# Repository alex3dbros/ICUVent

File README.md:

# ICUVent

Video Overview: https://youtu.be/w7vbeYg_BhQ

This project is opensource and there are no guarantees given that this device 
will perform the actions that it's needed to be. Please use it with care and 
under the surveilance of professionals.

Project Structure:

Inside 3DModels folder you have the solidworks 2019 and STL files 
Inside programming you will have the programming code used to control the device.
We started with Arduino Nano, stepper Driver and nema 23 motor.

You have the schematics of the circuit attached as well.

Parts used that must be purchased: 

Mechanics:
4 x 8mm round bearings from 3d printer
2 x 8mm rods
1 x Nema 34 Motor // Updated from nema 23, will update the design soon.
1 x 16 mm T5 belt
2 x 18 teeth T5 gear
1 x Ambubag, preferable with PEEP valve and safety valve

Electronics: 
1 x Teensy 3.2
1 x Driver PSD8079-2P
1 x Encoder like this : https://www.amazon.com/Cylewet-Encoder-Digital-Potentiometer-Arduino/dp/B07DM2YMT4/ref=sr_1_6?keywords=encoder&qid=1585150874&sr=8-6
1 x DC to DC 24V to 5V like this : https://www.amazon.com/6-5-28V-MP1584-DC-DC-Step-Down-Module/dp/B082957QHR/ref=sr_1_3?keywords=MP1584+5V&qid=1585150582&sr=8-3
1 x 24 V Power supply
1 x EndStop switch
1 x raspberry pi with 7 inch display
1 x MPXV5004DP
1 x MPXV5010DP

Connection pins - https://www.amazon.com/Hotop-Pack-Single-Header-Connector/dp/B06XR8CV8P/ref=sr_1_1?keywords=2.54+pins&qid=1585151123&sr=8-1&swrs=BA6CC27AC84D7760BA1186A07738C3A9

https://www.amazon.com/DEYUE-Jumper-Wires-Set-breadboard/dp/B07LFCLMGW/ref=sr_1_10?keywords=jumper+wires&qid=1585151157&sr=8-10

Connection wires

Some info about how I built it:

I 3D printed parts and cut at the CNC the larger ones.
Here's a video with the machine functional

All the best!

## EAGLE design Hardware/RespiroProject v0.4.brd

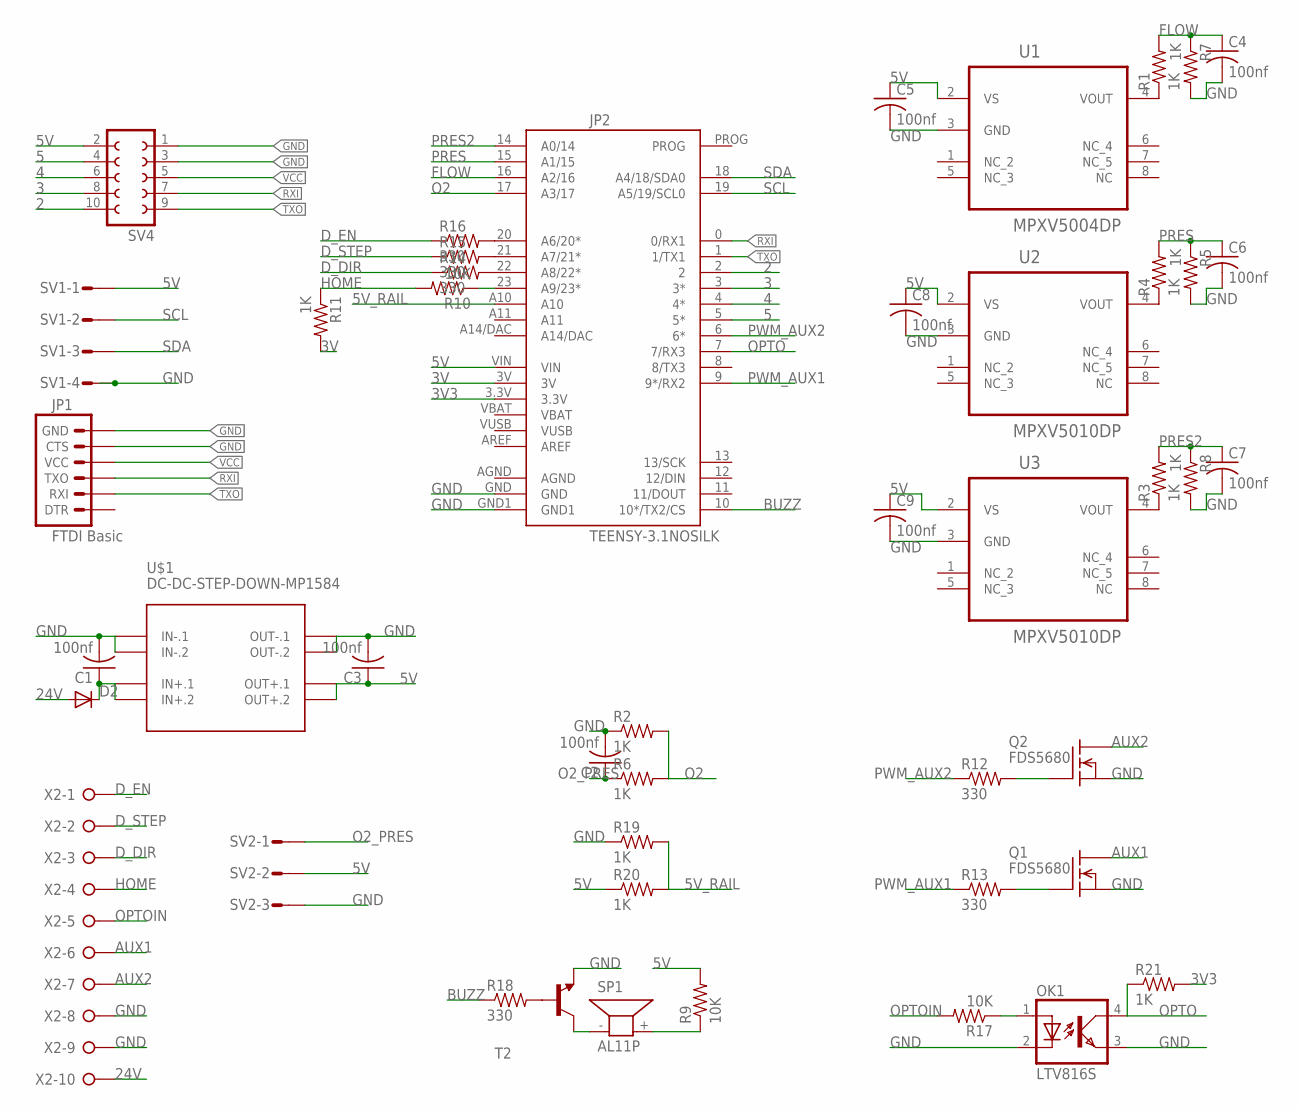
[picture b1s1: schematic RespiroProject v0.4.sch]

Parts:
C1, C2, C3, C4, C5, C6, C7, C8, C9: 100nf; C0805
D2: DIODE-MINIMELF; MINIMELF
JP1: FTDI Basic; 1X06
JP2: TEENSY-3.1NOSILK; TEENSY-3.1_NOSILK
OK1: LTV816S; DIL4-SMD
Q1, Q2: FDS5680; SO-8
R1, R2, R3, R4, R5, R6, R7, R8, R11, R19, R20, R21: 1K; 0805
R9, R10, R17: 10K; 0805
R12, R13, R14, R15, R16, R18: 330; 0805
SP1: AL11P
SV1: S04P
SV2: S03P
SV4: FE05-2
T2: BC817-16-NPN-SOT23-BEC; SOT23-BEC
U1: MPXV5004DP; FREESCALE_CASE_1351-01
U2, U3: MPXV5010DP; FREESCALE_CASE_1351-01
U$1: DC-DC-STEP-DOWN-MP1584
X2: W237-10P

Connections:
2: JP2.2, SV4.10
3: JP2.3 (3*), SV4.8
3V: JP2.3V, R11.2
3V3: JP2.3.3V, R21.2
4: JP2.4 (4*), SV4.6
5: JP2.5 (5*), SV4.4
5V: C3.1, C5.1, C8.1, C9.1, JP2.VIN, R9.2, R20.1, SV1.1, SV2.2, SV4.2, U1.2 (VS), U2.2 (VS), U3.2 (VS), U$1.OUT+.1, U$1.OUT+.2
5V_RAIL: JP2.A10, R19.2, R20.2
24V: D2.A, X2.10
AUX1: Q1.5 (D), Q1.6 (D), Q1.7 (D), Q1.8 (D), X2.6
AUX2: Q2.5 (D), Q2.6 (D), Q2.7 (D), Q2.8 (D), X2.7
BUZZ: JP2.10 (10*/TX2/CS), R18.1
D_DIR: R14.1, X2.3
D_EN: R16.1, X2.1
D_STEP: R15.1, X2.2
FLOW: C4.1, JP2.16 (A2/16), R1.2, R7.1
GND: C1.2, C2.2, C3.2, C4.2, C5.2, C6.2, C7.2, C8.2, C9.2, JP1.5 (CTS), JP1.6 (GND), JP2.GND, JP2.GND1, OK1.2 (C), OK1.3 (EMIT), Q1.1 (S), Q1.2 (S), Q1.3 (S), Q2.1 (S), Q2.2 (S), Q2.3 (S), R2.1, R5.2, R7.2, R8.2, R19.1, SV1.4, SV2.3, SV4.1, SV4.3, T2.E, U1.3 (GND), U2.3 (GND), U3.3 (GND), U$1.IN-.1, U$1.IN-.2, U$1.OUT-.1, U$1.OUT-.2, X2.8, X2.9
HOME: R10.2, R11.1, X2.4
unnamed: C1.1, D2.C, U$1.IN+.1, U$1.IN+.2
unnamed: R1.1, U1.4 (VOUT)
unnamed: R3.1, U3.4 (VOUT)
unnamed: R4.1, U2.4 (VOUT)
unnamed: SP1.- (1), T2.C
unnamed: R9.1, SP1.+ (2)
unnamed: JP2.23 (A9/23*), R10.1
unnamed: JP2.22 (A8/22*), R14.2
unnamed: Q2.4 (G), R12.2
unnamed: Q1.4 (G), R13.2
unnamed: JP2.21 (A7/21*), R15.2
unnamed: JP2.20 (A6/20*), R16.2
unnamed: OK1.1 (A), R17.1
unnamed: R18.2, T2.B
O2: JP2.17 (A3/17), R2.2, R6.2
O2_PRES: C2.1, R6.1, SV2.1
OPTO: JP2.7 (7/RX3), OK1.4 (COL), R21.1
OPTOIN: R17.2, X2.5
PRES: C6.1, JP2.15 (A1/15), R4.2, R5.1
PRES2: C7.1, JP2.14 (A0/14), R3.2, R8.1
PWM_AUX1: JP2.9 (9*/RX2), R13.1
PWM_AUX2: JP2.6 (6*), R12.1
RXI: JP1.3 (TXO), JP2.0 (0/RX1), SV4.7
SCL: JP2.19 (A5/19/SCL0), SV1.2
SDA: JP2.18 (A4/18/SDA0), SV1.3
TXO: JP1.2 (RXI), JP2.1 (1/TX1), SV4.9
VCC: JP1.4 (VCC), SV4.5

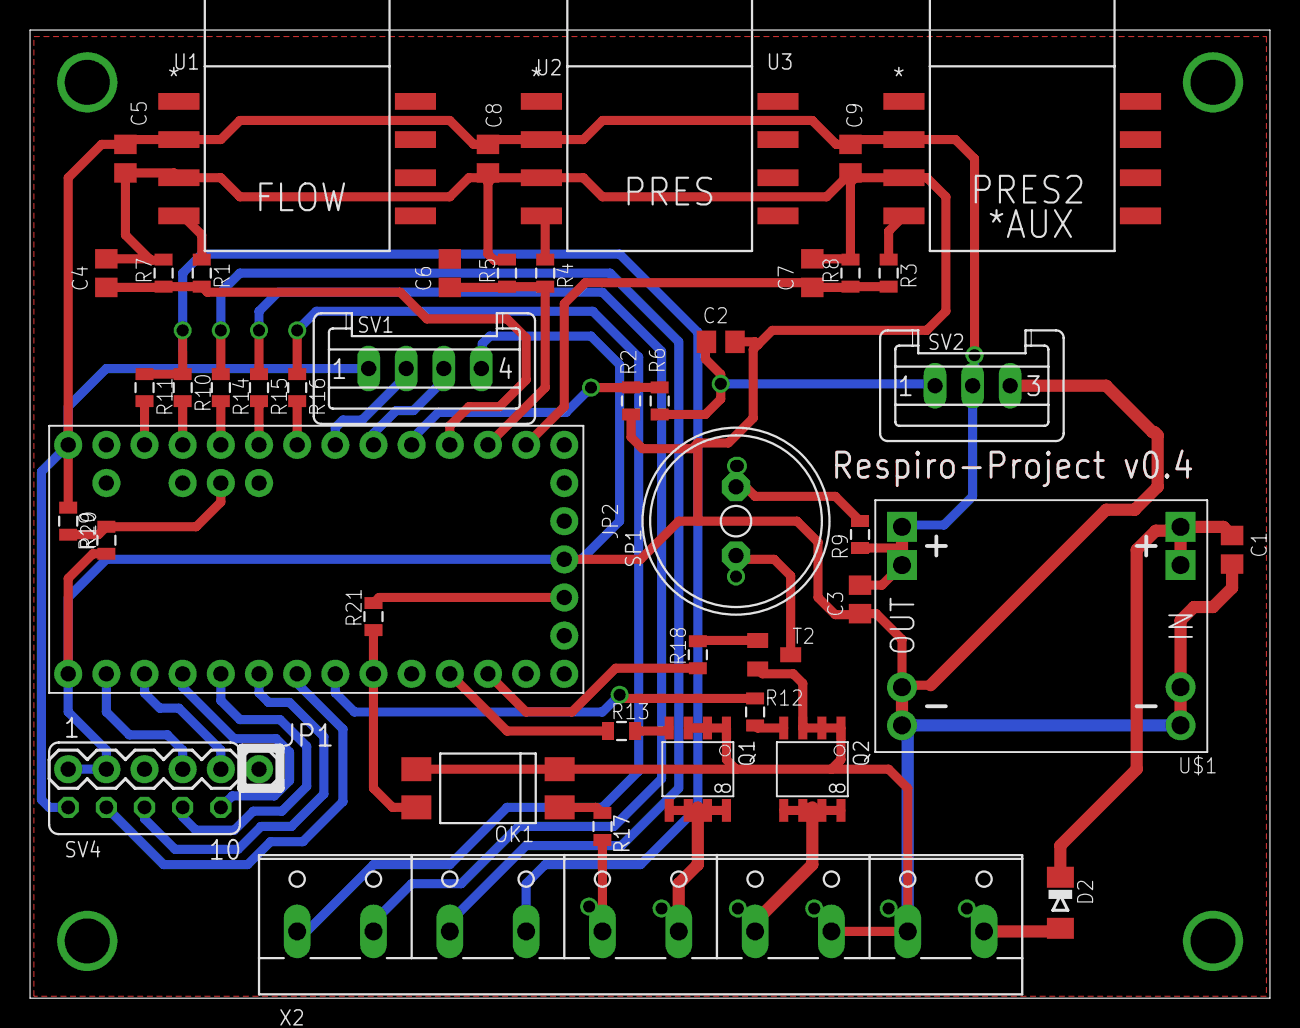
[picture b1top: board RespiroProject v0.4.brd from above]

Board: 2 copper layers, 82.5 x 64.4 mm, 46 parts (0 on the bottom side), 45 nets.

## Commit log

2020-03-25 First commit
    The software is done for debugging more, is not using controls a medic would use for breaths per minute etc.. planning to build a proper user interface
2020-03-25 Added STL Files
2020-03-26 Made the base middle hole larger, it was cumbersome to mount the belt
2020-03-26 Readme Edit
2020-03-26 Replaced gear belt tensioner with bearings and a screw
2020-03-27 Added the controller for teensy 3.2
    The new controller support uart (Serial) commands formatted in Json like {"breathsPerMinute":12, "airVol":600, "ieRate":2}
    I have also designed a venturi tube that's going to be used for volume measurement.
2020-03-29 added python interface
2020-03-30 Changed the stepper library to have better control of the stepper
2020-03-30 Updated readme, will be using nema 34
2020-03-30 Updated files to use nema 34 in the design
2020-04-01 Added gerber files of the new board and redesigned a bit
2020-04-03 Worked on some connection pieces
2020-04-03 Modified Pusher files
2020-04-04 Updated the bearings
2020-04-05 Added params for the nema 34 motor and 18 teeth gear
2020-04-06 Added step files, python interface is still WIP
2020-04-06 Solved character issue, added a ambu grabber part
2020-04-08 updated readme and added libraries
2020-04-09 Added IGS files
2020-04-10 Added IGS files for tubes
2020-04-11 Locked bar in place with a mirrored rod holder
2020-04-16 Added connection elements
2020-05-15 Added a check for pressed switch
2020-05-15 Added install mode for interface

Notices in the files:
parts and their libraries:
diy-modules: Released under the Creative Commons Attribution 4.0 International License: http://creativecommons.org/licenses/by/4.0
